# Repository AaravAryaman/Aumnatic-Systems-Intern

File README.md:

# Micro Drone Project @ Aumnatic Systems Pvt Ltd
Original Repo at [Aumnatic Toytronics](https://github.com/Aumnatic-Toytronics/Recreational-Hobby-Micro-Drone.git)  
  
I started my intern at Aumnatic Systems Pvt Ltd on 06/05/2024. The main objective of this intern project was to make a flying micro drone running on self-made flight controller. 
  
In the first week I started off with the Production Team, learning about procedures of PCB production with SMT (Surafce Mount Technology)- stencil printing, pick and place, reflow and quality check. I also tried hand soldering some components onto PCBs. Finally, I performed the testing of PCB circuits that had been produced for a fishing board toy. Meanwhile, I also began my [Drone Research](https://www.canva.com/design/DAGEteYy6_s/aPfHe0JrymGLhPgnTHX_pQ/view?utm_content=DAGEteYy6_s&utm_campaign=designshare&utm_medium=link&utm_source=editor) on various drone components, laws & regulations and the Indian drone industry online from countless sources available.  
  
In the second week I was with the Design R&D Team, learning about PCB designing. I learnt PCB designing in the KiCAD software which is free, instead of the Altium software being used by the team. Firstly, I made a CAD model [Drone Frame](https://github.com/Aumnatic-Toytronics/Recreational-Hobby-Micro-Drone/tree/main/Drone%20Frame) in Fusion360. Later, I made a complete PCB design of a [Motor Driver](https://github.com/Aumnatic-Toytronics/Recreational-Hobby-Micro-Drone/tree/main/Motor%20Driver) in KiCAD, from schematic capture and assigning footprints to PCB layouting and generating gerber files. As not all symbols and footprints were available in KiCAD by default, I also [Digikey's KiCAD Library](https://github.com/Digi-Key/digikey-kicad-library.git).  
  
In the third week, I researched some micro drones available in the market and tried to understand the process and code for a [ESP32 based drone](https://espressif-docs.readthedocs-hosted.com/projects/espressif-esp-drone/en/latest/index.html) system. At the end of the week I started my 1-week training at JSM Composites.  
  
In the week from 23/05 - 31/05/2024, I completed an [Intern at JSM Composites](https://github.com/AaravAryaman/JSM-Composites-Intern.git). Here, I learnt about use of composites in the industry. I learnt about manufacture of carbon fibre sheets and machining processes and how industry-ready products are made from these carbon fibres. I was also tasked with making new designs or modifying some existing designs in Fusion360.  
  
From the next week onwards (fourth week), I was back with the Design R&D Team at Aumnatic Systems Pvt Ltd. We had ordered [Pluto 1.2](https://www.dronaaviation.com/pluto-1-2/) drone manufactured by Drona Aviation. The purpose for this was to figure out any potential difficulties and challenges that might occur when assembling and flying a drone. The only major difficulty faced during this operation was of making the drone hover as the strcuture seemed to have some inherent imbalance. Then, I studied the documentations for the Pluto 1.2 drone and tried a modification of [Debug APIs](https://github.com/Aumnatic-Toytronics/Recreational-Hobby-Micro-Drone/tree/main/Debug%20APIs) in the drone. The sofware used was [Cygnus IDE](https://create.dronaaviation.com/software/drone-programming/cygnus-ide#downloads). The code was written in /src/main/PlutoPilot.cpp using debugging APIs like Utils.h and Estimate.h to show change in LED color as drone moves upward or downward or just remains stationary. The given code can be run after creating a new workspace in Cygnus IDE and following proper guidelines for building and flashing the code. Here's a video showing the working of the modification-  

https://github.com/Aumnatic-Toytronics/Recreational-Hobby-Micro-Drone/assets/131551391/0a625f74-dae5-4dba-b9b1-186422f1f15a  
  
In the fifth week, I made a ESP32 based [Flight Controller](https://github.com/Aumnatic-Toytronics/Recreational-Hobby-Micro-Drone/tree/main/Flight%20Controller) schematic in KiCAD. Assigning appropriate footprints to all component symbols and running ERC to resolve all errors and warnings. As not all symbols and footprints were available in KiCAD by default, I also [Digikey's KiCAD Library](https://github.com/Digi-Key/digikey-kicad-library.git). I had used the flight controller schematic of a ESPlane-V2-S2 drone as [Reference Schematic](https://espressif-docs.readthedocs-hosted.com/projects/espressif-esp-drone/en/latest/_static/ESPlane_V2_S2/SCH_ESPlane_V2_S2.pdf). I also made a PCB outline for this schematic in Fusion360 by referencing the [Primus V4](https://create.dronaaviation.com/hardware/flight-controllers/primus-v4) flight controller of Pluto 1.2, since this self-made flight controller will be used to replace of Pluto 1.2's flight controller to complete our project.  
  
In the sixth week, I started the study of [Crazyflie](https://github.com/bitcraze/crazyflie-firmware) and [ESP DSP Library](https://github.com/whyengineer/esp32-lin/tree/master/components/dsp_lib) source codes to be used in our ESP32 based flight controller to fly our drone. I also came across several open sourced self-projects available. I thoroughly went through the document regarding [ESP-IDF](https://docs.espressif.com/projects/esp-idf/en/latest/esp32s2/get-started/index.html) to learn the necesseties to build a project and flash it onto the device successfully.  
  
In the seventh week, while the self-made flight controller PCB was still in production, I 3D-printed the flight controller model after generating its g-code in Fusion360, to verify the mechanical design of the model. I used [Creality Ender-3 V2](https://www.crealitycloud.com/product/details/Ender-3-V2-6048caaf5852812341df35a6) for the 3D-print. I was also tasked with designing and 3D-printing a protective [USB-Camera Case](https://github.com/Aumnatic-Toytronics/Recreational-Hobby-Micro-Drone/tree/main/USB-Camera%20Case) in Fusion360.  
  
In the eighth and final week, I was tasked with designing a model for [Servo-Motor Motion-Sensing Gate Validator](https://github.com/Aumnatic-Toytronics/Recreational-Hobby-Micro-Drone/tree/main/Servo-Sensor%20Gate%20Validator) in Fusion360 that was then produced by laser cutting at Meta Branding. As my last task, I successfuly built a project and flashed it onto the self-made flight controller using [esp-drone](https://github.com/Aumnatic-Toytronics/Recreational-Hobby-Micro-Drone/tree/main/esp-drone). This code was sourced from [espressif esp-drone](https://github.com/espressif/esp-drone.git). To control the drone, I downloaded the [ESP-Drone App](https://www.pgyer.com/a27L) based on [ESP-Drone-Android](https://github.com/EspressifApps/ESP-Drone-Android), which used [Crazyflie-Android-Client](https://github.com/bitcraze/crazyflie-android-client) as source code. Following this, I concluded a successful flight test for the drone with all basic functions working as required.

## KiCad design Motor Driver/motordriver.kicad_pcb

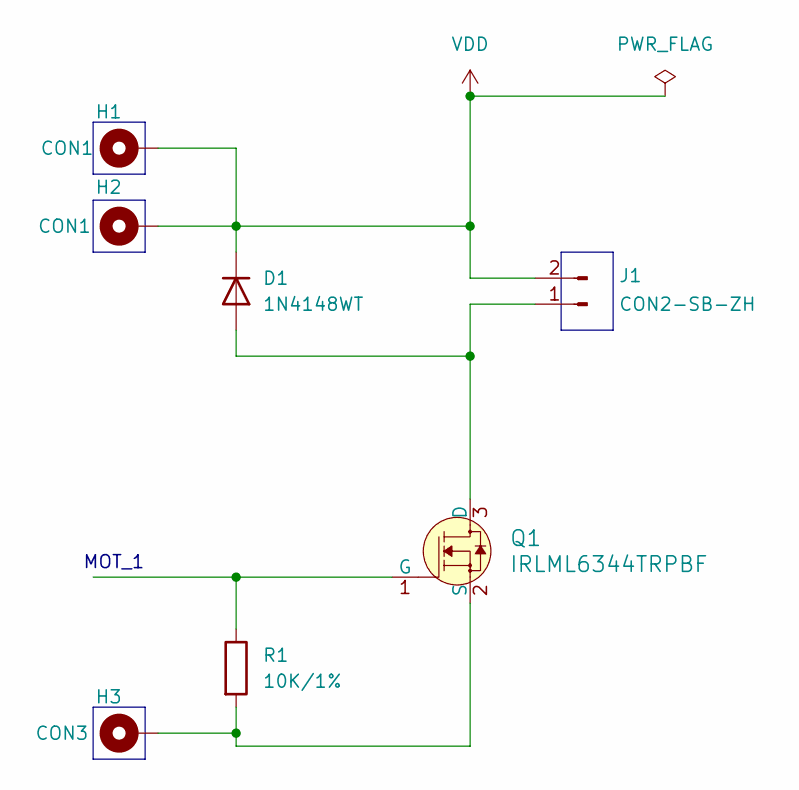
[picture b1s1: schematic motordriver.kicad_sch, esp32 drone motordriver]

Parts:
D1: 1N4148WT; D_SOD-523
H1, H2: CON1; H_Mounting_Pad_D0.8mm
H3: CON3; H_Mounting_Pad_D0.8mm
J1: CON2-SB-ZH; PinHeader_1x02_P2.00mm_Vertical
Q1: IRLML6344TRPBF; SOT-23-3; MPN IRLML6344TRPBF
R1: 10K/1%; R_0201_0603Metric

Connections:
unnamed: D1.2 (A), J1.1, Q1.3 (D)
unnamed: Q1.1 (G), R1.1
unnamed: H3.1, Q1.2 (S), R1.2
VDD: D1.1 (K), H1.1, H2.1, J1.2

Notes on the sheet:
MOT_1

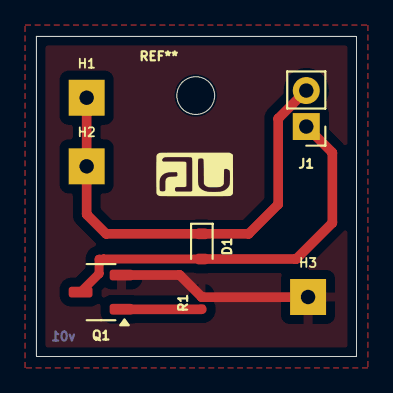
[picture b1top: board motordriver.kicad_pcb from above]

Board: 2 copper layers, 17.8 x 17.8 mm, 7 parts (0 on the bottom side), 4 nets.

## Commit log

2024-07-07 Add files
